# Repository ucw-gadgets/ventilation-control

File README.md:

# ventilation-control
Board for controlling ventilation system

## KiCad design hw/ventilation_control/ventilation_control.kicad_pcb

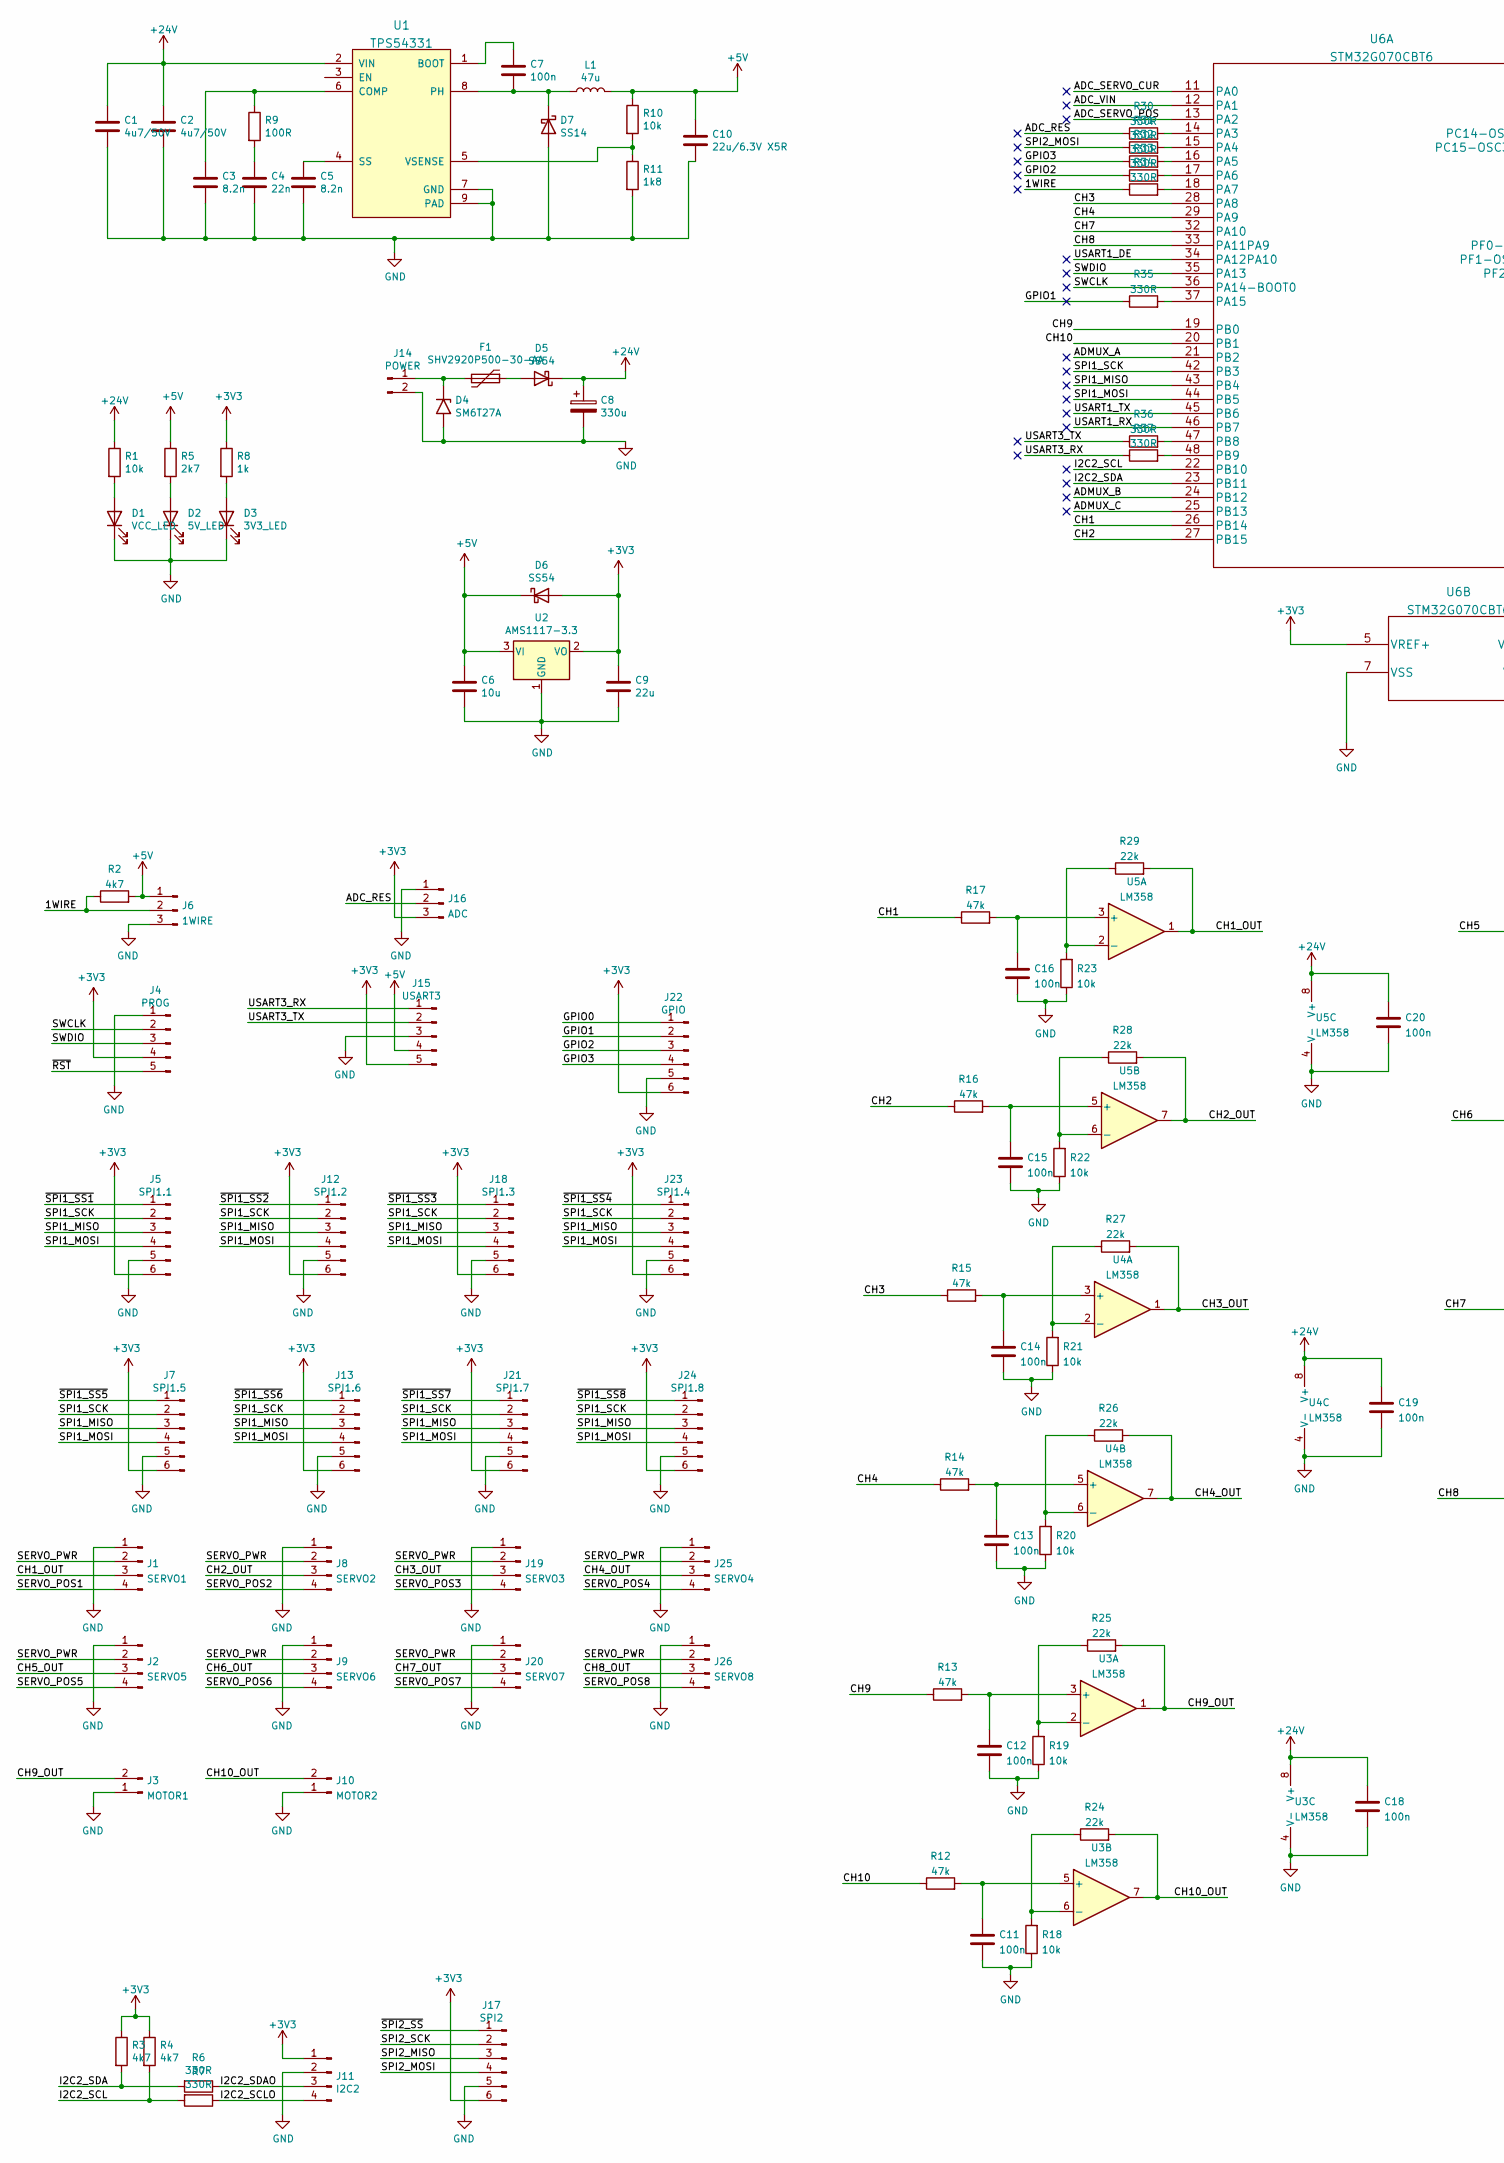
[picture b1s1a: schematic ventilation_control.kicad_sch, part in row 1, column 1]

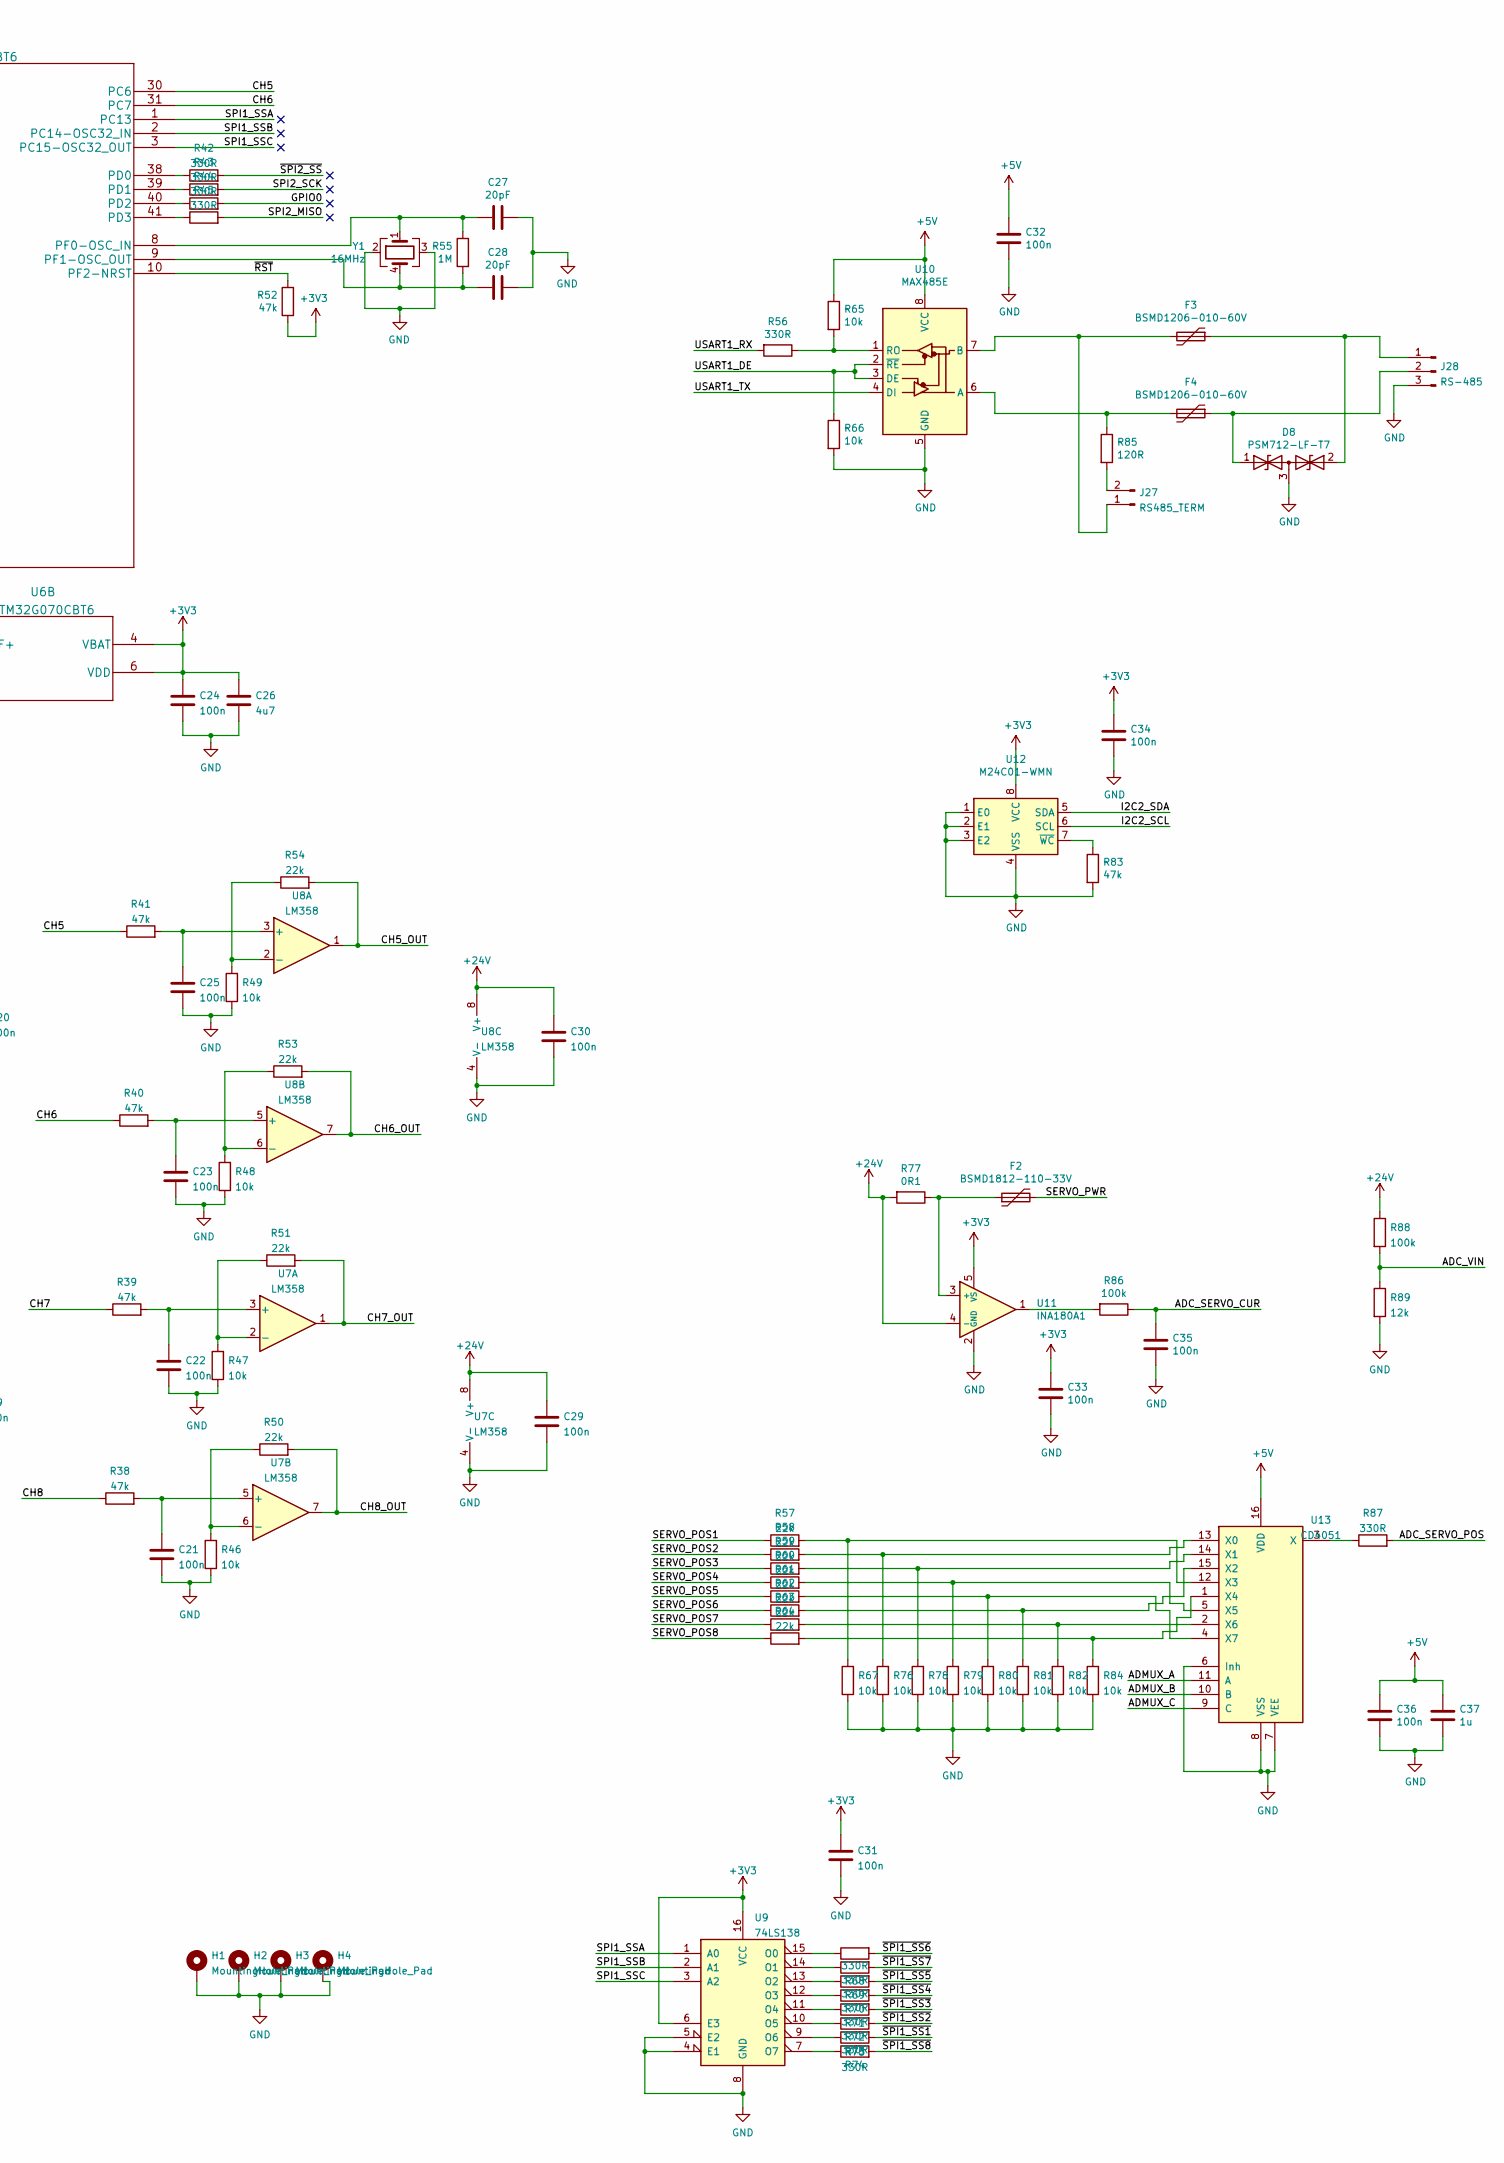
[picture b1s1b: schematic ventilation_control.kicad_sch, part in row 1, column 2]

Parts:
C1, C2: 4u7/50V; C_1206_3216Metric; LCSC C29823
C3, C5: 8.2n; C_0603_1608Metric; LCSC C27920
C4: 22n; C_0603_1608Metric; LCSC C21122
C6: 10u; C_0603_1608Metric; LCSC C19702
C7, C11, C12, C13, C14, C15, C16, C18, C19, C20, C21, C22, C23, C24, C25, C29, C30, C31, C32, C33, C34, C35, C36: 100n; C_0603_1608Metric; LCSC C14663
C8: 330u; CP_Radial_D10.0mm_P5.00mm
C9: 22u; C_0603_1608Metric; LCSC C59461
C10: 22u/6.3V X5R; C_0603_1608Metric; LCSC C59461
C26: 4u7; C_1206_3216Metric; LCSC C29823
C27, C28: 20pF; C_0603_1608Metric; LCSC C1648
C37: 1u; C_0603_1608Metric; LCSC C15849
D1: VCC_LED; LED_0603_1608Metric; LCSC C72043
D2: 5V_LED; LED_0603_1608Metric; LCSC C72043
D3: 3V3_LED; LED_0603_1608Metric; LCSC C72043
D4: SM6T27A; D_SMB; LCSC C133693
D5, D6: SS54; D_SMA; LCSC C22452
D7: SS14; D_SMA; LCSC C2480
D8: PSM712-LF-T7; SOT-23; LCSC C32677
F1: SHV2920P500-30-AA; Fuse_2920_7451Metric; LCSC C495350
F2: BSMD1812-110-33V; Fuse_1812_4532Metric; LCSC C883150
F3, F4: BSMD1206-010-60V; Fuse_1206_3216Metric; LCSC C883116
H1, H2, H3, H4: MountingHole_Pad; MountingHole_3.2mm_M3_Pad_Via
J1: SERVO1; Molex_KK-254_AE-6410-04A_1x04_P2.54mm_Vertical
J2: SERVO5; Molex_KK-254_AE-6410-04A_1x04_P2.54mm_Vertical
J3: MOTOR1; Molex_KK-254_AE-6410-02A_1x02_P2.54mm_Vertical
J4: PROG; Molex_KK-254_AE-6410-05A_1x05_P2.54mm_Vertical
J5: SPI1.1; Molex_KK-254_AE-6410-06A_1x06_P2.54mm_Vertical
J6: 1WIRE; Molex_KK-254_AE-6410-03A_1x03_P2.54mm_Vertical
J7: SPI1.5; Molex_KK-254_AE-6410-06A_1x06_P2.54mm_Vertical
J8: SERVO2; Molex_KK-254_AE-6410-04A_1x04_P2.54mm_Vertical
J9: SERVO6; Molex_KK-254_AE-6410-04A_1x04_P2.54mm_Vertical
J10: MOTOR2; Molex_KK-254_AE-6410-02A_1x02_P2.54mm_Vertical
J11: I2C2; Molex_KK-254_AE-6410-04A_1x04_P2.54mm_Vertical
J12: SPI1.2; Molex_KK-254_AE-6410-06A_1x06_P2.54mm_Vertical
J13: SPI1.6; Molex_KK-254_AE-6410-06A_1x06_P2.54mm_Vertical
J14: POWER; PhoenixContact_MCV_1,5_2-GF-3.81_1x02_P3.81mm_Vertical_Thre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
J15: USART3; Molex_KK-254_AE-6410-05A_1x05_P2.54mm_Vertical
J16: ADC; Molex_KK-254_AE-6410-03A_1x03_P2.54mm_Vertical
J17: SPI2; Molex_KK-254_AE-6410-06A_1x06_P2.54mm_Vertical
J18: SPI1.3; Molex_KK-254_AE-6410-06A_1x06_P2.54mm_Vertical
J19: SERVO3; Molex_KK-254_AE-6410-04A_1x04_P2.54mm_Vertical
J20: SERVO7; Molex_KK-254_AE-6410-04A_1x04_P2.54mm_Vertical
J21: SPI1.7; Molex_KK-254_AE-6410-06A_1x06_P2.54mm_Vertical
J22: GPIO; Molex_KK-254_AE-6410-06A_1x06_P2.54mm_Vertical
J23: SPI1.4; Molex_KK-254_AE-6410-06A_1x06_P2.54mm_Vertical
J24: SPI1.8; Molex_KK-254_AE-6410-06A_1x06_P2.54mm_Vertical
J25: SERVO4; Molex_KK-254_AE-6410-04A_1x04_P2.54mm_Vertical
J26: SERVO8; Molex_KK-254_AE-6410-04A_1x04_P2.54mm_Vertical
J27: RS485_TERM; PinHeader_1x02_P2.54mm_Vertical
J28: RS-485; PhoenixContact_MCV_1,5_3-G-3.81_1x03_P3.81mm_Vertical
L1: 47u; L_Bourns_SRP7028A_7.3x6.6mm; LCSC C436585
R1, R10, R18, R19, R20, R21, R22, R23, R46, R47, R48, R49, R65, R66, R67, R76, R78, R79, R80, R81, R82, R84: 10k; R_0603_1608Metric; LCSC C25804
R2, R3, R4: 4k7; R_0603_1608Metric; LCSC C23162
R5: 2k7; R_0603_1608Metric; LCSC C13167
R6, R7, R30, R31, R32, R33, R34, R35, R36, R37, R42, R43, R44, R45, R56, R68, R69, R70, R71, R72, R73, R74, R75, R87: 330R; R_0603_1608Metric; LCSC C23138
R8: 1k; R_0603_1608Metric; LCSC C21190
R9: 100R; R_0603_1608Metric; LCSC C22775
R11: 1k8; R_0603_1608Metric; LCSC C4177
R12, R13, R14, R15, R16, R17, R38, R39, R40, R41, R52, R83: 47k; R_0603_1608Metric; LCSC C25819
R24, R25, R26, R27, R28, R29, R50, R51, R53, R54, R57, R58, R59, R60, R61, R62, R63, R64: 22k; R_0603_1608Metric; LCSC C31850
R55: 1M; R_0603_1608Metric; LCSC C22935
R77: 0R1; R_1206_3216Metric; LCSC C25334
R85: 120R; R_0603_1608Metric; LCSC C22787
R86, R88: 100k; R_0603_1608Metric; LCSC C25803
R89: 12k; R_0603_1608Metric; LCSC C22790
U1: TPS54331; SOIC-8_3.9x4.9mm_P1.27mm; LCSC C9865
U2: AMS1117-3.3; SOT-223-3_TabPin2; LCSC C6186
U3, U4, U5, U7, U8: LM358; SO-8_3.9x4.9mm_P1.27mm; LCSC C7950
U6: STM32G070CBT6; LQFP-48_7x7mm_P0.5mm
U9: 74LS138; SO-16_3.9x9.9mm_P1.27mm; LCSC C5602
U10: MAX485E; SOIC-8_3.9x4.9mm_P1.27mm; LCSC C6855
U11: INA180A1; SOT-23-5; LCSC C122228
U12: M24C01-WMN; SOIC-8_3.9x4.9mm_P1.27mm; LCSC C79988
U13: CD4051; SO-16_3.9x9.9mm_P1.27mm; LCSC C21379
Y1: 16MHz; Crystal_SMD_3225-4Pin_3.2x2.5mm; LCSC C13738

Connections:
+3V3: C9.1, C24.1, C26.1, C31.1, C33.1, C34.1, D6.2 (A), J4.4, J5.6, J7.6, J11.1, J12.6, J13.6, J15.5, J16.3, J17.6, J18.6, J21.6, J22.6, J23.6, J24.6, R3.1, R4.1, R8.1, R52.2, U2.2 (VO), U6.4 (VBAT), U6.5 (VREF+), U6.6 (VDD), U9.6 (E3), U9.16 (VCC), U11.5 (VS), U12.8 (VCC)
+5V: C6.1, C10.1, C32.1, C36.1, C37.1, D6.1 (K), J6.1, J15.4, L1.2, R2.2, R5.1, R10.1, R65.1, U2.3 (VI), U10.8 (VCC), U13.16 (VDD)
+24V: C1.1, C2.1, C8.1, C18.1, C19.1, C20.1, C29.1, C30.1, D5.1 (K), R1.1, R77.2, R88.1, U1.2 (VIN), U3.8 (V+), U4.8 (V+), U5.8 (V+), U7.8 (V+), U8.8 (V+), U11.4 (-)
/1WIRE: J6.2, R2.1, R34.1
/ADC_RES: J16.2, R30.1
/ADC_SERVO_CUR: C35.1, R86.1, U6.11 (PA0)
/ADC_SERVO_POS: R87.2, U6.13 (PA2)
/ADC_VIN: R88.2, R89.1, U6.12 (PA1)
/ADMUX_A: U6.21 (PB2), U13.11 (A)
/ADMUX_B: U6.24 (PB12), U13.10 (B)
/ADMUX_C: U6.25 (PB13), U13.9 (C)
/CH1: R17.1, U6.26 (PB14)
/CH1_OUT: J1.3, R29.2, U5.1
/CH2: R16.1, U6.27 (PB15)
/CH2_OUT: J8.3, R28.2, U5.7
/CH3: R15.1, U6.28 (PA8)
/CH3_OUT: J19.3, R27.2, U4.1
/CH4: R14.1, U6.29 (PA9)
/CH4_OUT: J25.3, R26.2, U4.7
/CH5: R41.1, U6.30 (PC6)
/CH5_OUT: J2.3, R54.2, U8.1
/CH6: R40.1, U6.31 (PC7)
/CH6_OUT: J9.3, R53.2, U8.7
/CH7: R39.1, U6.32 (PA10)
/CH7_OUT: J20.3, R51.2, U7.1
/CH8: R38.1, U6.33 (PA11PA9)
/CH8_OUT: J26.3, R50.2, U7.7
/CH9: R13.1, U6.19 (PB0)
/CH9_OUT: J3.2, R25.2, U3.1
/CH10: R12.1, U6.20 (PB1)
/CH10_OUT: J10.2, R24.2, U3.7
/GPIO0: J22.1, R44.2
/GPIO1: J22.2, R35.1
/GPIO2: J22.3, R33.1
/GPIO3: J22.4, R32.1
/I2C2_SCL: R4.2, R7.2, U6.22 (PB10), U12.6 (SCL)
/I2C2_SCLO: J11.4, R7.1
/I2C2_SDA: R3.2, R6.2, U6.23 (PB11), U12.5 (SDA)
/I2C2_SDAO: J11.3, R6.1
/SERVO_POS1: J1.4, R57.1
/SERVO_POS2: J8.4, R58.1
/SERVO_POS3: J19.4, R59.1
/SERVO_POS4: J25.4, R60.1
/SERVO_POS5: J2.4, R61.1
/SERVO_POS6: J9.4, R62.1
/SERVO_POS7: J20.4, R63.1
/SERVO_POS8: J26.4, R64.1
/SERVO_PWR: F2.2, J1.2, J2.2, J8.2, J9.2, J19.2, J20.2, J25.2, J26.2
/SPI1_MISO: J5.3, J7.3, J12.3, J13.3, J18.3, J21.3, J23.3, J24.3, U6.43 (PB4)
/SPI1_MOSI: J5.4, J7.4, J12.4, J13.4, J18.4, J21.4, J23.4, J24.4, U6.44 (PB5)
/SPI1_SCK: J5.2, J7.2, J12.2, J13.2, J18.2, J21.2, J23.2, J24.2, U6.42 (PB3)
/SPI1_SSA: U6.1 (PC13), U9.1 (A0)
/SPI1_SSB: U6.2 (PC14-OSC32_IN), U9.2 (A1)
/SPI1_SSC: U6.3 (PC15-OSC32_OUT), U9.3 (A2)
/SPI2_MISO: J17.3, R45.2
/SPI2_MOSI: J17.4, R31.1
/SPI2_SCK: J17.2, R43.2
/SWCLK: J4.2, U6.36 (PA14-BOOT0)
/SWDIO: J4.3, U6.35 (PA13)
/USART1_DE: R66.1, U6.34 (PA12PA10), U10.2 (~RE), U10.3 (DE)
/USART1_RX: R56.2, U6.46 (PB7)
/USART1_TX: U6.45 (PB6), U10.4 (DI)
/USART3_RX: J15.1, R37.1
/USART3_TX: J15.2, R36.1
/~RST: J4.5, R52.1, U6.10 (PF2-NRST)
/~SPI1_SS1: J5.1, R74.2
/~SPI1_SS2: J12.1, R73.2
/~SPI1_SS3: J18.1, R72.2
/~SPI1_SS4: J23.1, R71.2
/~SPI1_SS5: J7.1, R70.2
/~SPI1_SS6: J13.1, R68.2
/~SPI1_SS7: J21.1, R69.2
/~SPI1_SS8: J24.1, R75.2
/~SPI2_SS: J17.1, R42.2
GND: C1.2, C2.2, C3.2, C4.2, C5.2, C6.2, C8.2, C9.2, C10.2, C11.2, C12.2, C13.2, C14.2, C15.2, C16.2, C18.2, C19.2, C20.2, C21.2, C22.2, C23.2, C24.2, C25.2, C26.2, C27.2, C28.2, C29.2, C30.2, C31.2, C32.2, C33.2, C34.2, C35.2, C36.2, C37.2, D1.1 (K), D2.1 (K), D3.1 (K), D4.2 (A2), D7.2 (A), D8.3 (common), H1.1, H2.1, H3.1, H4.1, J1.1, J2.1, J3.1, J4.1, J5.5, J6.3, J7.5, J8.1, J9.1, J10.1, J11.2, J12.5, J13.5, J14.2, J15.3, J16.1, J17.5, J18.5, J19.1, J20.1, J21.5, J22.5, J23.5, J24.5, J25.1, J26.1, J28.3, R11.2, R18.1, R19.1, R20.1, R21.1, R22.1, R23.1, R46.1, R47.1, R48.1, R49.1, R66.2, R67.1, R76.1, R78.1, R79.1, R80.1, R81.1, R82.1, R83.2, R84.1, R89.2, U1.7 (GND), U1.9 (PAD), U2.1 (GND), U3.4 (V-), U4.4 (V-), U5.4 (V-), U6.7 (VSS), U7.4 (V-), U8.4 (V-), U9.4 (E1), U9.5 (E2), U9.8 (GND), U10.5 (GND), U11.2 (GND), U12.1 (E0), U12.2 (E1), U12.3 (E2), U12.4 (VSS), U13.6 (Inh), U13.7 (VEE), U13.8 (VSS), Y1.2, Y1.3
unnamed: C3.1, R9.1, U1.6 (COMP)
unnamed: C4.1, R9.2
unnamed: C5.1, U1.4 (SS)
unnamed: C7.1, U1.1 (BOOT)
unnamed: C7.2, D7.1 (K), L1.1, U1.8 (PH)
unnamed: C11.1, R12.2, U3.5 (+)
unnamed: C12.1, R13.2, U3.3 (+)
unnamed: C13.1, R14.2, U4.5 (+)
unnamed: C14.1, R15.2, U4.3 (+)
unnamed: C15.1, R16.2, U5.5 (+)
unnamed: C16.1, R17.2, U5.3 (+)
unnamed: C21.1, R38.2, U7.5 (+)
unnamed: C22.1, R39.2, U7.3 (+)
unnamed: C23.1, R40.2, U8.5 (+)
unnamed: C25.1, R41.2, U8.3 (+)
unnamed: C27.1, R55.1, U6.8 (PF0-OSC_IN), Y1.1
unnamed: C28.1, R55.2, U6.9 (PF1-OSC_OUT), Y1.4
unnamed: D1.2 (A), R1.2
unnamed: D2.2 (A), R5.2
unnamed: D3.2 (A), R8.2
unnamed: D4.1 (A1), F1.2, J14.1
unnamed: D5.2 (A), F1.1
unnamed: D8.1 (A1), F4.1, J28.2
unnamed: D8.2 (A2), F3.1, J28.1
unnamed: F2.1, R77.1, U11.3 (+)
unnamed: F3.2, J27.1, U10.7 (B)
unnamed: F4.2, R85.1, U10.6 (A)
unnamed: J27.2, R85.2
unnamed: R10.2, R11.1, U1.5 (VSENSE)
unnamed: R18.2, R24.1, U3.6 (-)
unnamed: R19.2, R25.1, U3.2 (-)
unnamed: R20.2, R26.1, U4.6 (-)
unnamed: R21.2, R27.1, U4.2 (-)
unnamed: R22.2, R28.1, U5.6 (-)
unnamed: R23.2, R29.1, U5.2 (-)
unnamed: R30.2, U6.14 (PA3)
unnamed: R31.2, U6.15 (PA4)
unnamed: R32.2, U6.16 (PA5)
unnamed: R33.2, U6.17 (PA6)
unnamed: R34.2, U6.18 (PA7)
unnamed: R35.2, U6.37 (PA15)
unnamed: R36.2, U6.47 (PB8)
unnamed: R37.2, U6.48 (PB9)
unnamed: R42.1, U6.38 (PD0)
unnamed: R43.1, U6.39 (PD1)
unnamed: R44.1, U6.40 (PD2)
unnamed: R45.1, U6.41 (PD3)
unnamed: R46.2, R50.1, U7.6 (-)
unnamed: R47.2, R51.1, U7.2 (-)
unnamed: R48.2, R53.1, U8.6 (-)
unnamed: R49.2, R54.1, U8.2 (-)
unnamed: R56.1, R65.2, U10.1 (RO)
unnamed: R57.2, R67.2, U13.12 (X3)
unnamed: R58.2, R76.2, U13.13 (X0)
unnamed: R59.2, R78.2, U13.14 (X1)
unnamed: R60.2, R79.2, U13.5 (X5)
unnamed: R61.2, R80.2, U13.4 (X7)
unnamed: R62.2, R81.2, U13.15 (X2)
unnamed: R63.2, R82.2, U13.2 (X6)
unnamed: R64.2, R84.2, U13.1 (X4)
unnamed: R68.1, U9.15 (O0)
unnamed: R69.1, U9.14 (O1)
unnamed: R70.1, U9.13 (O2)
unnamed: R71.1, U9.12 (O3)
unnamed: R72.1, U9.11 (O4)
unnamed: R73.1, U9.10 (O5)
unnamed: R74.1, U9.9 (O6)
unnamed: R75.1, U9.7 (O7)
unnamed: R83.1, U12.7 (~WC)
unnamed: R86.2, U11.1
unnamed: R87.1, U13.3 (X)

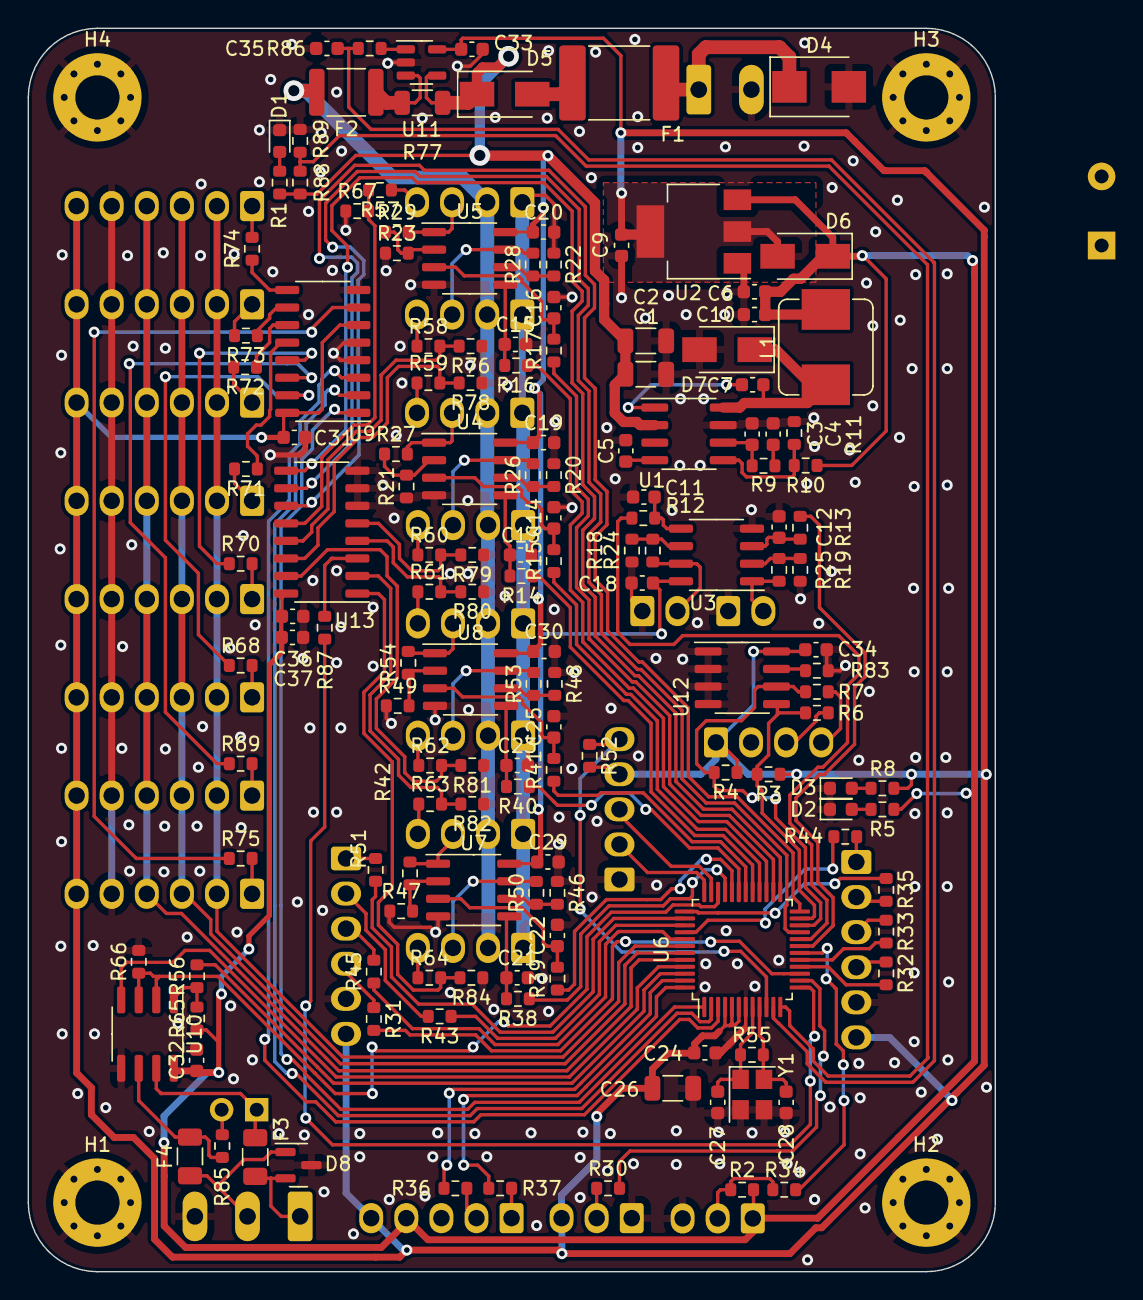
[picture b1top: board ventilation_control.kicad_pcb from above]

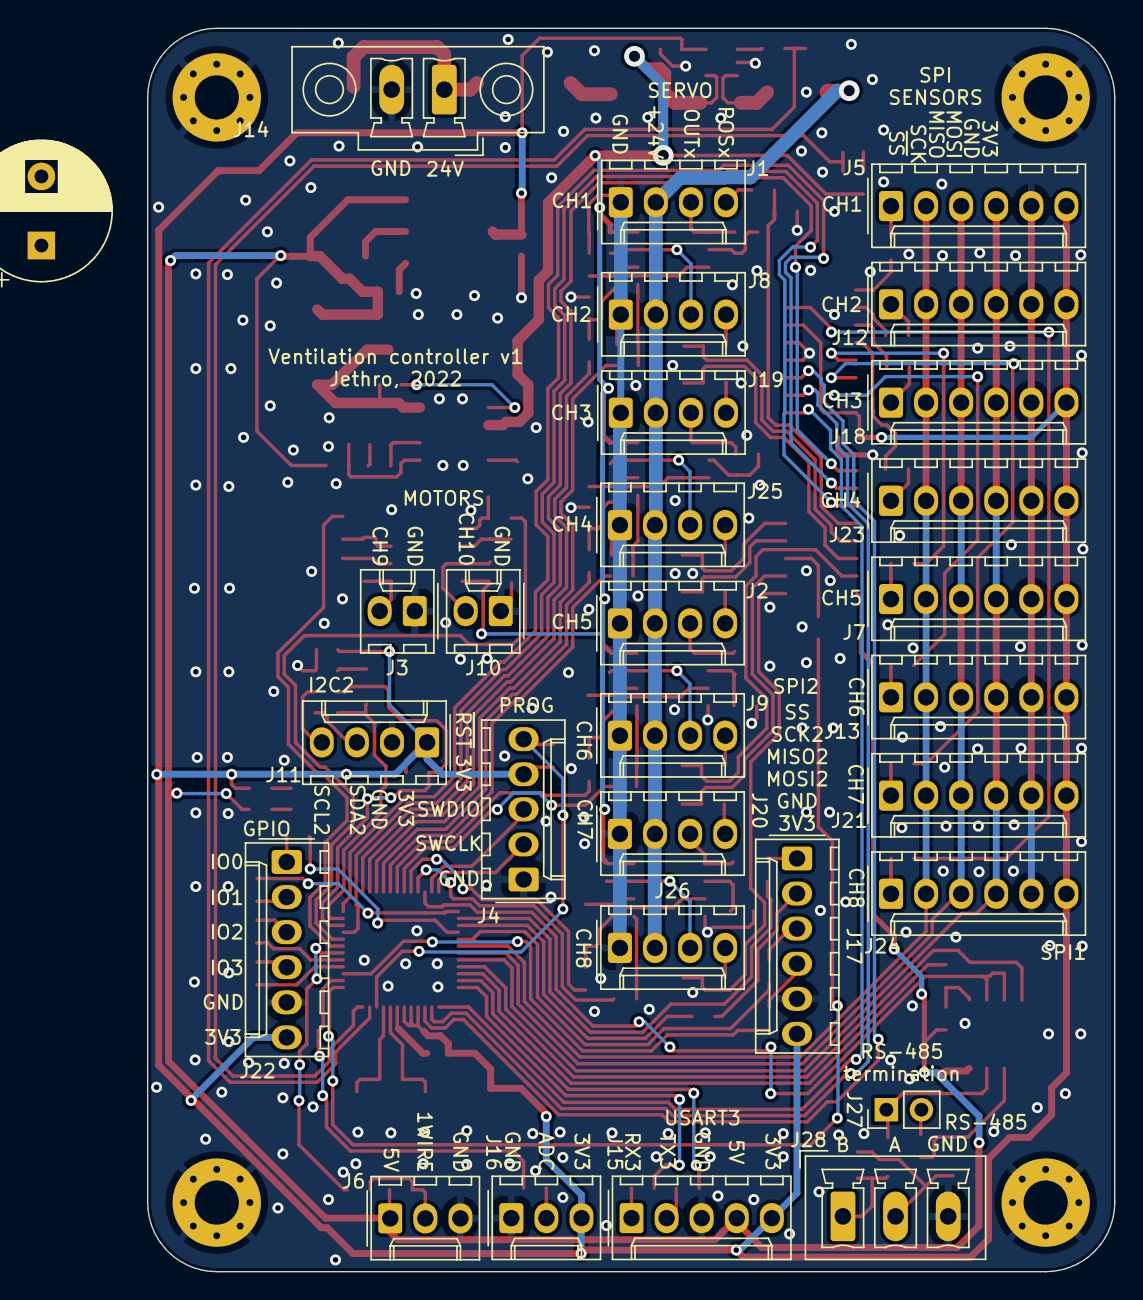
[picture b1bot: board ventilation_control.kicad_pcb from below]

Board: 2 copper layers, 70.0 x 90.0 mm, 184 parts (29 on the bottom side), 146 nets.

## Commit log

2022-02-03 Added schematic and board.
2022-02-05 Final changes.
